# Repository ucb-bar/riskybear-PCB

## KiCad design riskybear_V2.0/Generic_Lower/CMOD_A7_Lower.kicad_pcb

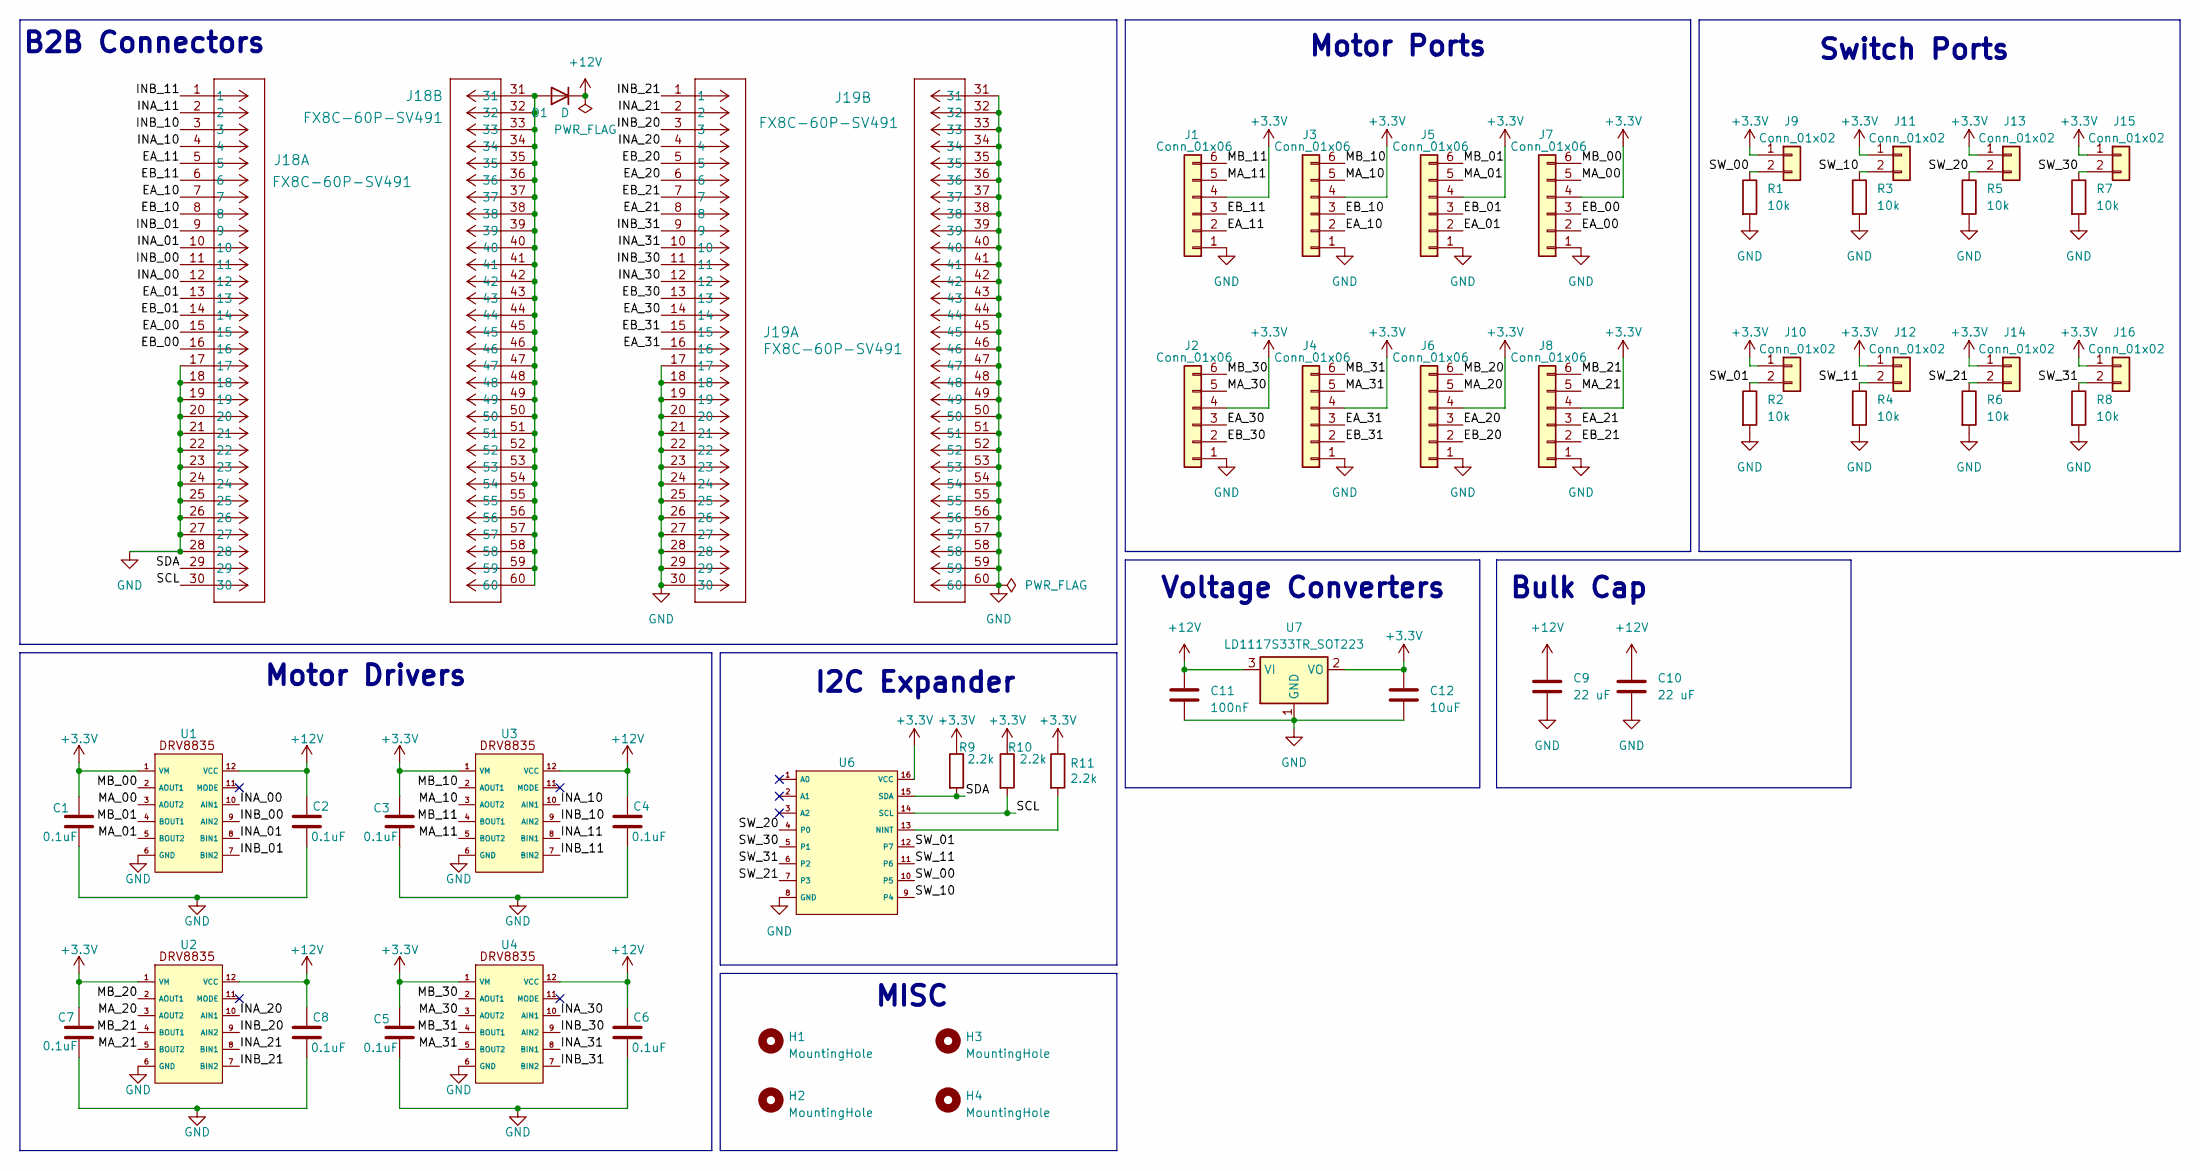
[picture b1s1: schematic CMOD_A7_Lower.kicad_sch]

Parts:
C1, C2, C3, C4, C5, C6, C7, C8: 0.1uF; C_0805_2012Metric
C9, C10: 22 uF; CP_Radial_D5.0mm_P2.00mm
C11: 100nF; C_0805_2012Metric
C12: 10uF; C_0805_2012Metric
D1: D; D_SOD-128
H1, H2, H3, H4: MountingHole; MountingHole_3.2mm_M3
J1, J2, J3, J4, J5, J6, J7, J8: Conn_01x06; JST_SH_BM06B-SRSS-TB_1x06-1MP_P1.00mm_Vertical
J9, J10, J11, J12, J13, J14, J15, J16: Conn_01x02; JST_GH_SM02B-GHS-TB_1x02-1MP_P1.25mm_Horizontal
J18, J19: FX8C-60P-SV491; CONN_P-SV491
R1, R2, R3, R4, R5, R6, R7, R8: 10k; R_0603_1608Metric_Pad0.98x0.95mm_HandSolder
R9, R10, R11: 2.2k; R_0603_1608Metric_Pad0.98x0.95mm_HandSolder
U1, U2, U3, U4: TDFN-12_2x3mm_P0.5mm
U6: TSSOP-16-1EP_4.4x5mm_P0.65mm
U7: LD1117S33TR_SOT223; SOT-223-3_TabPin2

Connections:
+3.3V: C1.1, C3.1, C5.1, C7.1, C12.1, J1.4, J2.4, J3.4, J4.4, J5.4, J6.4, J7.4, J8.4, J9.1, J10.1, J11.1, J12.1, J13.1, J14.1, J15.1, J16.1, R9.1, R10.1, R11.1, U1.1 (VM), U2.1 (VM), U3.1 (VM), U4.1 (VM), U6.16 (VCC), U7.2 (VO)
+12V: C2.1, C4.1, C6.1, C8.1, C9.1, C10.1, C11.1, D1.1 (K), U1.12 (VCC), U2.12 (VCC), U3.12 (VCC), U4.12 (VCC), U7.3 (VI)
/EA_00: J7.2, J18.15
/EA_01: J5.2, J18.13
/EA_10: J3.2, J18.7
/EA_11: J1.2, J18.5
/EA_20: J6.3, J19.6
/EA_21: J8.3, J19.8
/EA_30: J2.3, J19.14
/EA_31: J4.3, J19.16
/EB_00: J7.3, J18.16
/EB_01: J5.3, J18.14
/EB_10: J3.3, J18.8
/EB_11: J1.3, J18.6
/EB_20: J6.2, J19.5
/EB_21: J8.2, J19.7
/EB_30: J2.2, J19.13
/EB_31: J4.2, J19.15
/INA_00: J18.12, U1.10 (AIN1)
/INA_01: J18.10, U1.8 (BIN1)
/INA_10: J18.4, U3.10 (AIN1)
/INA_11: J18.2, U3.8 (BIN1)
/INA_20: J19.4, U2.10 (AIN1)
/INA_21: J19.2, U2.8 (BIN1)
/INA_30: J19.12, U4.10 (AIN1)
/INA_31: J19.10, U4.8 (BIN1)
/INB_00: J18.11, U1.9 (AIN2)
/INB_01: J18.9, U1.7 (BIN2)
/INB_10: J18.3, U3.9 (AIN2)
/INB_11: J18.1, U3.7 (BIN2)
/INB_20: J19.3, U2.9 (AIN2)
/INB_21: J19.1, U2.7 (BIN2)
/INB_30: J19.11, U4.9 (AIN2)
/INB_31: J19.9, U4.7 (BIN2)
/MA_00: J7.5, U1.3 (AOUT2)
/MA_01: J5.5, U1.5 (BOUT2)
/MA_10: J3.5, U3.3 (AOUT2)
/MA_11: J1.5, U3.5 (BOUT2)
/MA_20: J6.5, U2.3 (AOUT2)
/MA_21: J8.5, U2.5 (BOUT2)
/MA_30: J2.5, U4.3 (AOUT2)
/MA_31: J4.5, U4.5 (BOUT2)
/MB_00: J7.6, U1.2 (AOUT1)
/MB_01: J5.6, U1.4 (BOUT1)
/MB_10: J3.6, U3.2 (AOUT1)
/MB_11: J1.6, U3.4 (BOUT1)
/MB_20: J6.6, U2.2 (AOUT1)
/MB_21: J8.6, U2.4 (BOUT1)
/MB_30: J2.6, U4.2 (AOUT1)
/MB_31: J4.6, U4.4 (BOUT1)
/SCL: J18.30, R10.2, U6.14 (SCL)
/SDA: J18.29, R9.2, U6.15 (SDA)
/SW_00: J9.2, R1.1, U6.10 (P5)
/SW_01: J10.2, R2.1, U6.12 (P7)
/SW_10: J11.2, R3.1, U6.9 (P4)
/SW_11: J12.2, R4.1, U6.11 (P6)
/SW_20: J13.2, R5.1, U6.4 (P0)
/SW_21: J14.2, R6.1, U6.7 (P3)
/SW_30: J15.2, R7.1, U6.5 (P1)
/SW_31: J16.2, R8.1, U6.6 (P2)
GND: C1.2, C2.2, C3.2, C4.2, C5.2, C6.2, C7.2, C8.2, C9.2, C10.2, C11.2, C12.2, J1.1, J2.1, J3.1, J4.1, J5.1, J6.1, J7.1, J8.1, J18.17, J18.18, J18.19, J18.20, J18.21, J18.22, J18.23, J18.24, J18.25, J18.26, J18.27, J18.28, J19.17, J19.18, J19.19, J19.20, J19.21, J19.22, J19.23, J19.24, J19.25, J19.26, J19.27, J19.28, J19.29, J19.30, J19.31, J19.32, J19.33, J19.34, J19.35, J19.36, J19.37, J19.38, J19.39, J19.40, J19.41, J19.42, J19.43, J19.44, J19.45, J19.46, J19.47, J19.48, J19.49, J19.50, J19.51, J19.52, J19.53, J19.54, J19.55, J19.56, J19.57, J19.58, J19.59, J19.60, R1.2, R2.2, R3.2, R4.2, R5.2, R6.2, R7.2, R8.2, U1.6 (GND), U2.6 (GND), U3.6 (GND), U4.6 (GND), U6.8 (GND), U7.1 (GND)
unnamed: D1.2 (A), J18.31, J18.32, J18.33, J18.34, J18.35, J18.36, J18.37, J18.38, J18.39, J18.40, J18.41, J18.42, J18.43, J18.44, J18.45, J18.46, J18.47, J18.48, J18.49, J18.50, J18.51, J18.52, J18.53, J18.54, J18.55, J18.56, J18.57, J18.58, J18.59, J18.60
unnamed: R11.2, U6.13 (NINT)

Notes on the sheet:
B2B Connectors
Bulk Cap
Voltage Converters
I2C Expander
Motor Ports
Switch Ports
MISC
Motor Drivers

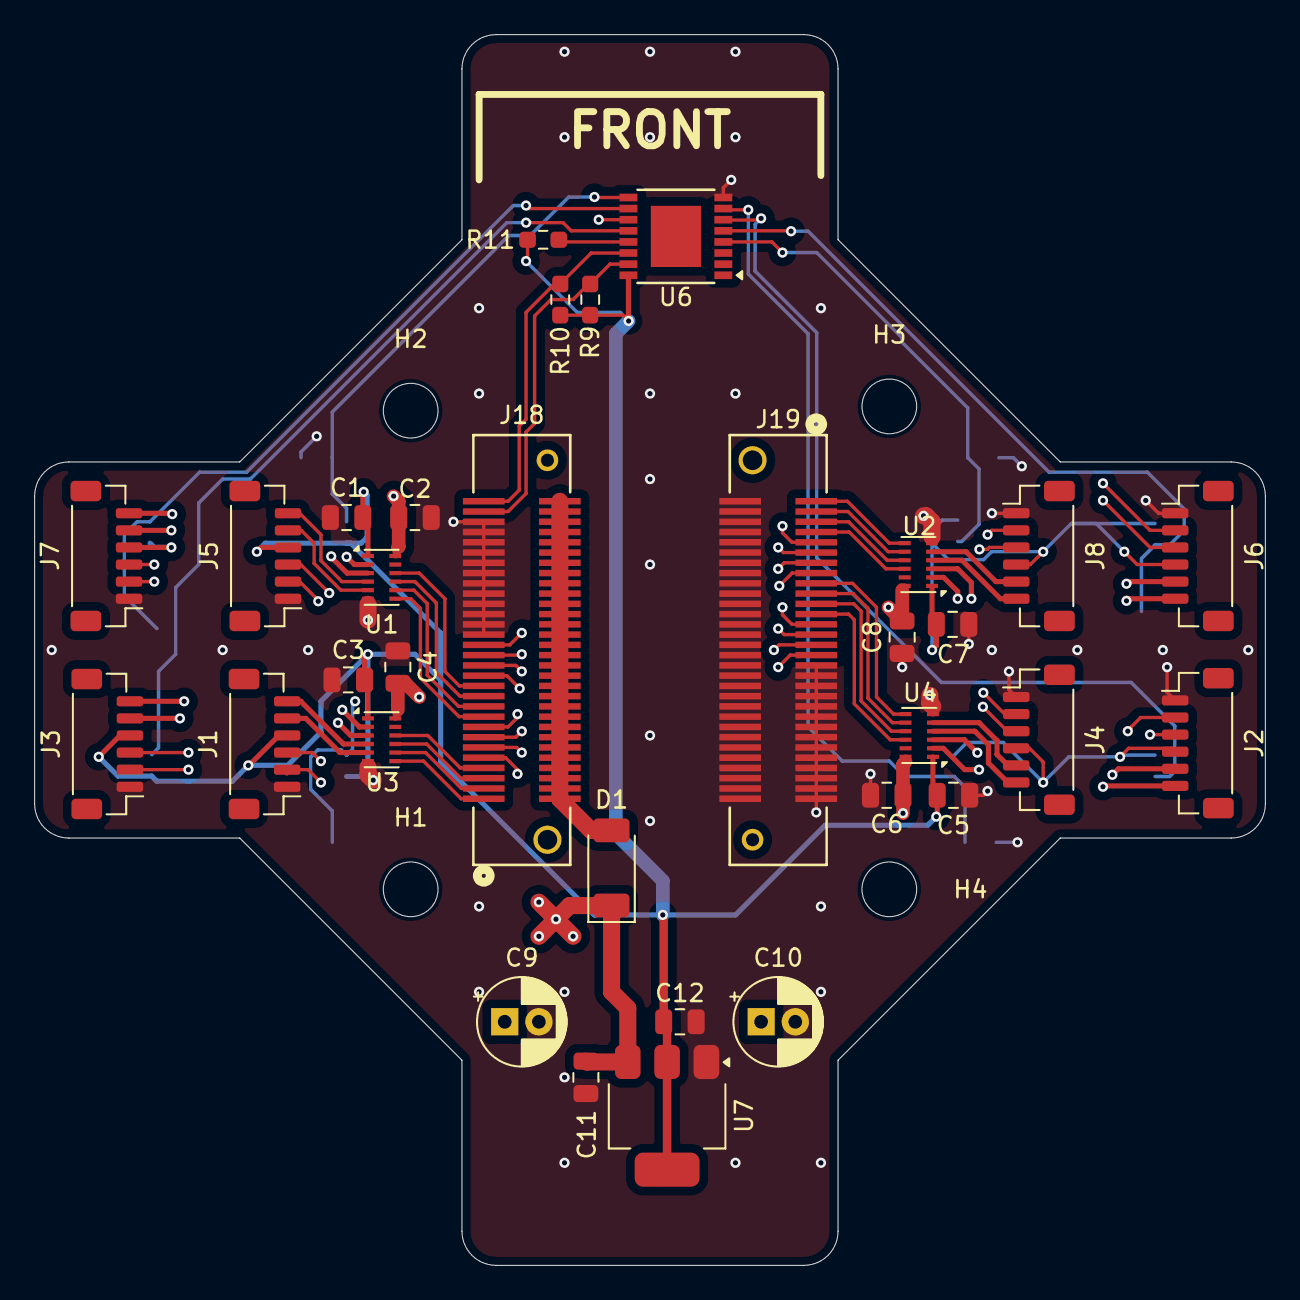
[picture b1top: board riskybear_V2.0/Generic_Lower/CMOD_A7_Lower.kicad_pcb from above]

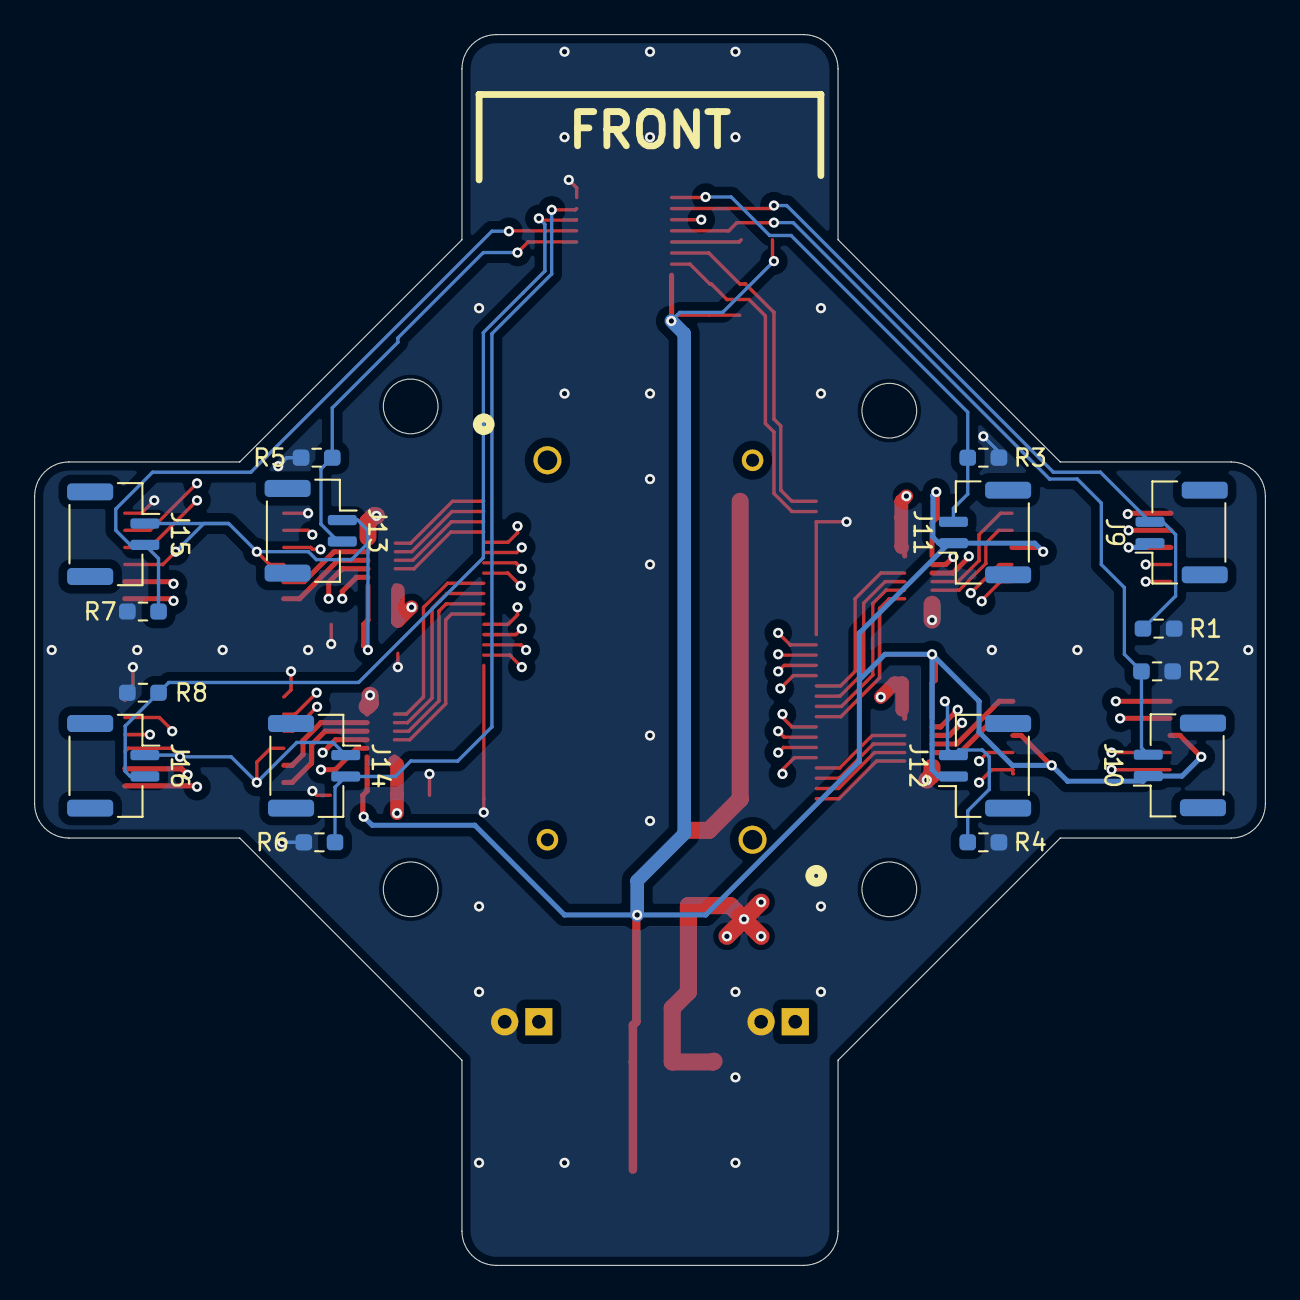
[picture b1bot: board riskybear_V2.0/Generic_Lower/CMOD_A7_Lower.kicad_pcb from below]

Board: 4 copper layers, 72.0 x 72.0 mm, 52 parts (16 on the bottom side), 63 nets.

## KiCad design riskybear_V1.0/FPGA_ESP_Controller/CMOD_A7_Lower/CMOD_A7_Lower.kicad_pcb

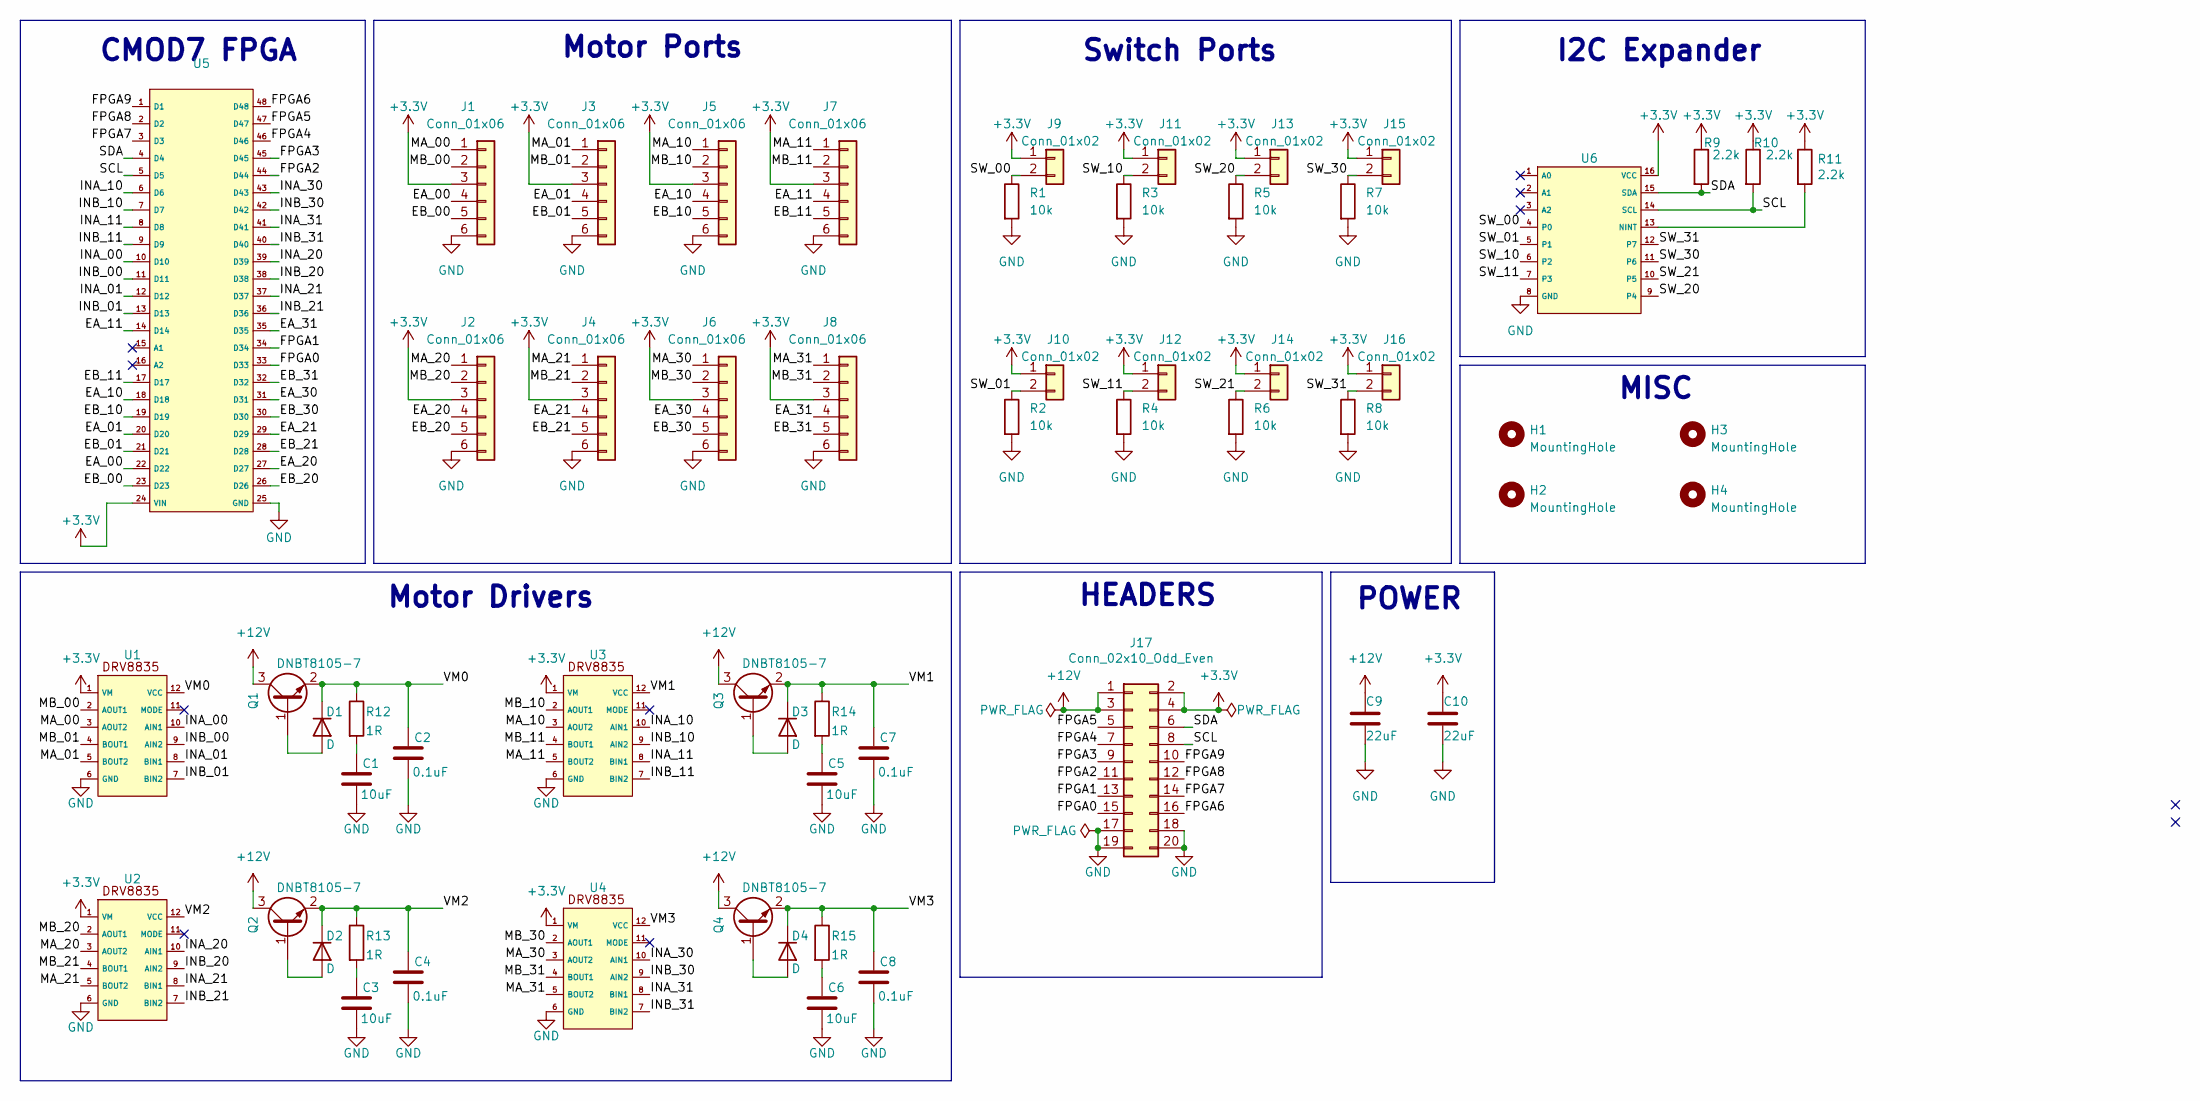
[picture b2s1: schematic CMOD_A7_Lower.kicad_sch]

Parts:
C1, C3, C5, C6: 10uF; C_0805_2012Metric
C2, C4, C7, C8: 0.1uF; C_0805_2012Metric
C9, C10: 22uF; CP_Radial_D5.0mm_P2.00mm
D1, D2, D3, D4: D; D_SMA
H1, H2, H3, H4: MountingHole; MountingHole_3.2mm_M3
J1, J2, J3, J4, J5, J6, J7, J8: Conn_01x06; JST_SH_BM06B-SRSS-TB_1x06-1MP_P1.00mm_Vertical
J9, J10, J11, J12, J13, J14, J15, J16: Conn_01x02; PinHeader_1x02_P2.54mm_Vertical_SMD_Pin1Left
J17: Conn_02x10_Odd_Even; PinHeader_2x10_P2.54mm_Vertical
Q1, Q2, Q3, Q4: DNBT8105-7; SOT-23
R1, R2, R3, R4, R5, R6, R7, R8: 10k; R_0603_1608Metric_Pad0.98x0.95mm_HandSolder
R9, R10, R11: 2.2k; R_0603_1608Metric_Pad0.98x0.95mm_HandSolder
R12, R13, R14, R15: 1R; C_0603_1608Metric
U1, U2, U3, U4: TDFN-12_2x3mm_P0.5mm
U5: CMODA7
U6: TSSOP-16-1EP_4.4x5mm_P0.65mm

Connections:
+3.3V: C10.1, J1.3, J2.3, J3.3, J4.3, J5.3, J6.3, J7.3, J8.3, J9.1, J10.1, J11.1, J12.1, J13.1, J14.1, J15.1, J16.1, J17.2, J17.4, R9.1, R10.1, R11.1, U1.1 (VM), U2.1 (VM), U3.1 (VM), U4.1 (VM), U5.24 (VIN), U6.16 (VCC)
+12V: C9.1, J17.1, J17.3, Q1.3 (C), Q2.3 (C), Q3.3 (C), Q4.3 (C)
/EA_00: J1.4, U5.22 (D22)
/EA_01: J3.4, U5.20 (D20)
/EA_10: J5.4, U5.18 (D18)
/EA_11: J7.4, U5.14 (D14)
/EA_20: J2.4, U5.27 (D27)
/EA_21: J4.4, U5.29 (D29)
/EA_30: J6.4, U5.31 (D31)
/EA_31: J8.4, U5.35 (D35)
/EB_00: J1.5, U5.23 (D23)
/EB_01: J3.5, U5.21 (D21)
/EB_10: J5.5, U5.19 (D19)
/EB_11: J7.5, U5.17 (D17)
/EB_20: J2.5, U5.26 (D26)
/EB_21: J4.5, U5.28 (D28)
/EB_30: J6.5, U5.30 (D30)
/EB_31: J8.5, U5.32 (D32)
/FPGA0: J17.15, U5.33 (D33)
/FPGA1: J17.13, U5.34 (D34)
/FPGA2: J17.11, U5.44 (D44)
/FPGA3: J17.9, U5.45 (D45)
/FPGA4: J17.7, U5.46 (D46)
/FPGA5: J17.5, U5.47 (D47)
/FPGA6: J17.16, U5.48 (D48)
/FPGA7: J17.14, U5.3 (D3)
/FPGA8: J17.12, U5.2 (D2)
/FPGA9: J17.10, U5.1 (D1)
/INA_00: U1.10 (AIN1), U5.10 (D10)
/INA_01: U1.8 (BIN1), U5.12 (D12)
/INA_10: U3.10 (AIN1), U5.6 (D6)
/INA_11: U3.8 (BIN1), U5.8 (D8)
/INA_20: U2.10 (AIN1), U5.39 (D39)
/INA_21: U2.8 (BIN1), U5.37 (D37)
/INA_30: U4.10 (AIN1), U5.43 (D43)
/INA_31: U4.8 (BIN1), U5.41 (D41)
/INB_00: U1.9 (AIN2), U5.11 (D11)
/INB_01: U1.7 (BIN2), U5.13 (D13)
/INB_10: U3.9 (AIN2), U5.7 (D7)
/INB_11: U3.7 (BIN2), U5.9 (D9)
/INB_20: U2.9 (AIN2), U5.38 (D38)
/INB_21: U2.7 (BIN2), U5.36 (D36)
/INB_30: U4.9 (AIN2), U5.42 (D42)
/INB_31: U4.7 (BIN2), U5.40 (D40)
/MA_00: J1.1, U1.3 (AOUT2)
/MA_01: J3.1, U1.5 (BOUT2)
/MA_10: J5.1, U3.3 (AOUT2)
/MA_11: J7.1, U3.5 (BOUT2)
/MA_20: J2.1, U2.3 (AOUT2)
/MA_21: J4.1, U2.5 (BOUT2)
/MA_30: J6.1, U4.3 (AOUT2)
/MA_31: J8.1, U4.5 (BOUT2)
/MB_00: J1.2, U1.2 (AOUT1)
/MB_01: J3.2, U1.4 (BOUT1)
/MB_10: J5.2, U3.2 (AOUT1)
/MB_11: J7.2, U3.4 (BOUT1)
/MB_20: J2.2, U2.2 (AOUT1)
/MB_21: J4.2, U2.4 (BOUT1)
/MB_30: J6.2, U4.2 (AOUT1)
/MB_31: J8.2, U4.4 (BOUT1)
/SCL: J17.8, R10.2, U5.5 (D5), U6.14 (SCL)
/SDA: J17.6, R9.2, U5.4 (D4), U6.15 (SDA)
/SW_00: J9.2, R1.1, U6.4 (P0)
/SW_01: J10.2, R2.1, U6.5 (P1)
/SW_10: J11.2, R3.1, U6.6 (P2)
/SW_11: J12.2, R4.1, U6.7 (P3)
/SW_20: J13.2, R5.1, U6.9 (P4)
/SW_21: J14.2, R6.1, U6.10 (P5)
/SW_30: J15.2, R7.1, U6.11 (P6)
/SW_31: J16.2, R8.1, U6.12 (P7)
/VM0: C2.1, D1.1 (K), Q1.2 (E), R12.1, U1.12 (VCC)
/VM1: C7.1, D3.1 (K), Q3.2 (E), R14.1, U3.12 (VCC)
/VM2: C4.1, D2.1 (K), Q2.2 (E), R13.1, U2.12 (VCC)
/VM3: C8.1, D4.1 (K), Q4.2 (E), R15.1, U4.12 (VCC)
GND: C1.2, C2.2, C3.2, C4.2, C5.2, C6.2, C7.2, C8.2, C9.2, C10.2, J1.6, J2.6, J3.6, J4.6, J5.6, J6.6, J7.6, J8.6, J17.17, J17.18, J17.19, J17.20, R1.2, R2.2, R3.2, R4.2, R5.2, R6.2, R7.2, R8.2, U1.6 (GND), U2.6 (GND), U3.6 (GND), U4.6 (GND), U5.25 (GND), U6.8 (GND)
unnamed: C1.1, R12.2
unnamed: C3.1, R13.2
unnamed: C5.1, R14.2
unnamed: C6.1, R15.2
unnamed: D1.2 (A), Q1.1 (B)
unnamed: D2.2 (A), Q2.1 (B)
unnamed: D3.2 (A), Q3.1 (B)
unnamed: D4.2 (A), Q4.1 (B)
unnamed: R11.2, U6.13 (NINT)

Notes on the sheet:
CMOD7 FPGA
I2C Expander
Motor Ports
Switch Ports
POWER
MISC
Motor Drivers
HEADERS

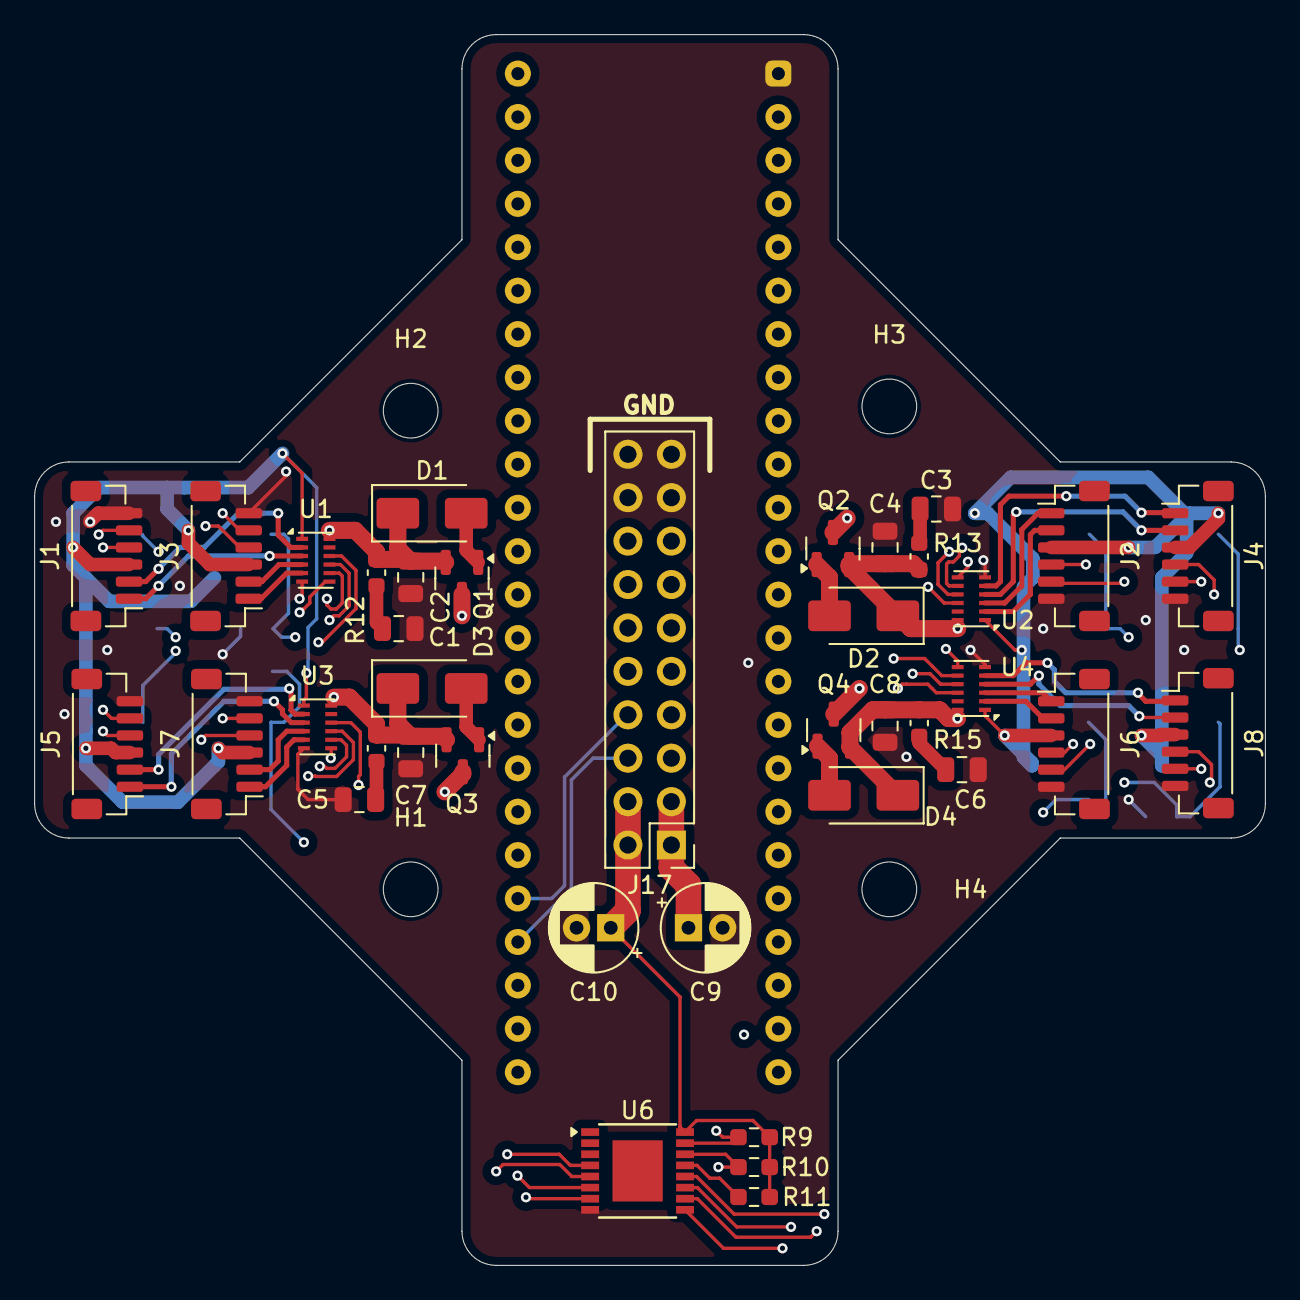
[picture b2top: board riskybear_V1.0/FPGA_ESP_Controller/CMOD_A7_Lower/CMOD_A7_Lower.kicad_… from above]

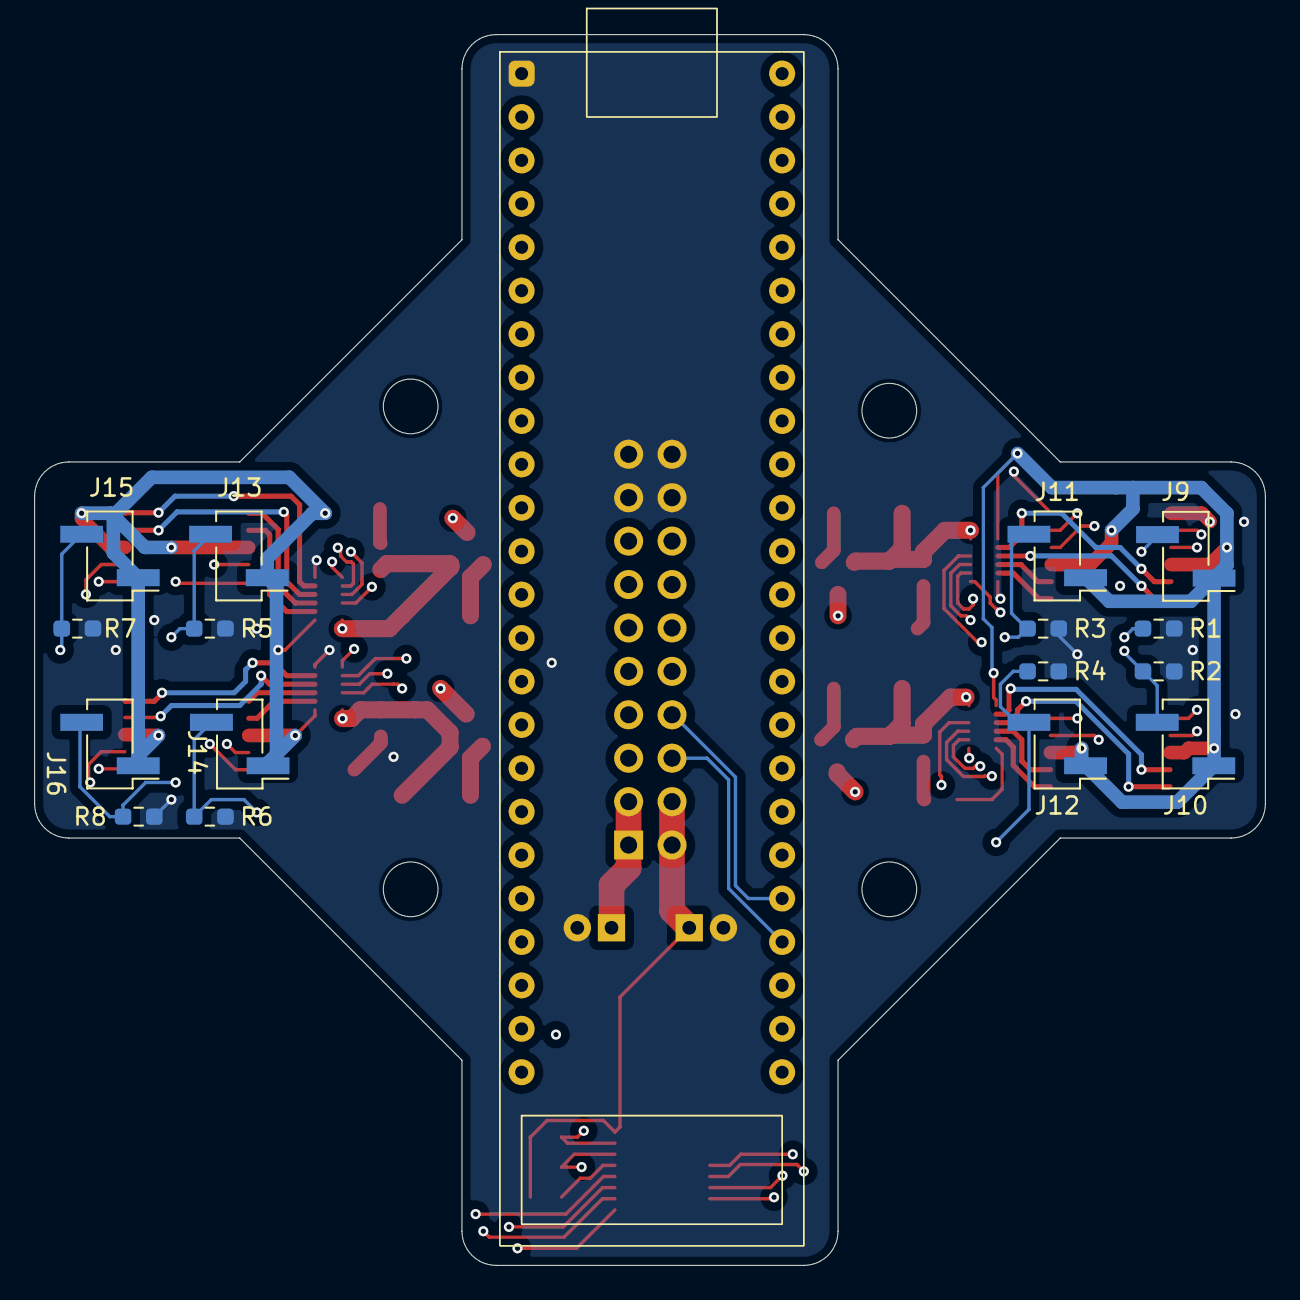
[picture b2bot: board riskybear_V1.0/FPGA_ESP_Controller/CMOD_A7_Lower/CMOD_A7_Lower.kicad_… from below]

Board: 4 copper layers, 72.0 x 72.0 mm, 60 parts (17 on the bottom side), 84 nets.

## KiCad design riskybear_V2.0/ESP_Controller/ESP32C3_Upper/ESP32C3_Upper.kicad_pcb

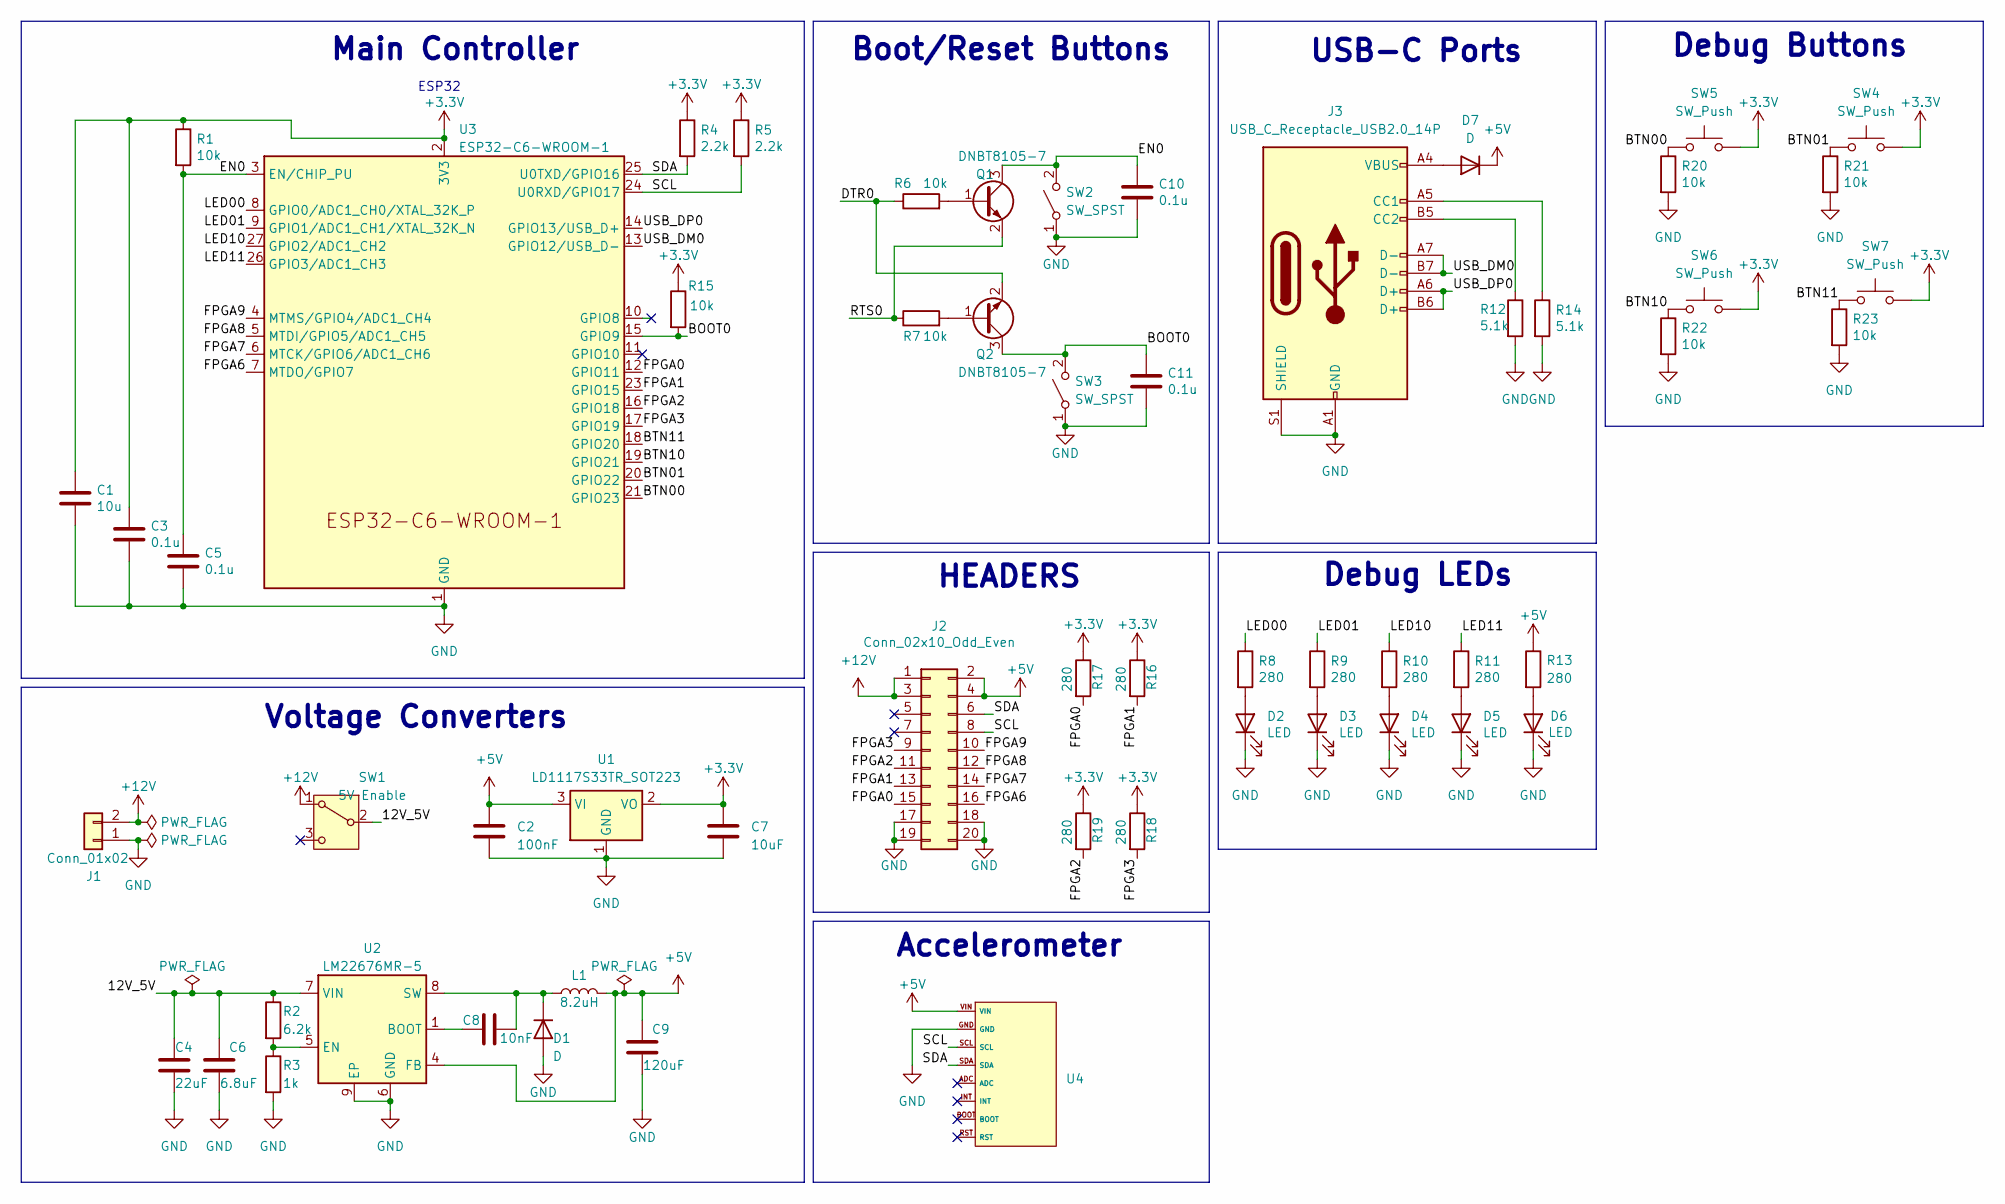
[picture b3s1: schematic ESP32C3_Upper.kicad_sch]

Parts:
C1: 10u; C_0603_1608Metric_Pad1.08x0.95mm_HandSolder
C2: 100nF; C_0805_2012Metric
C3, C5, C10, C11: 0.1u; C_0603_1608Metric_Pad1.08x0.95mm_HandSolder
C4: 22uF; CP_Radial_D5.0mm_P2.00mm
C6: 6.8uF; C_0805_2012Metric
C7: 10uF; C_0805_2012Metric
C8: 10nF; C_0805_2012Metric
C9: 120uF; CP_Radial_D6.3mm_P2.50mm
D1, D7: D; D_SMA_Handsoldering
D2, D3, D4, D5, D6: LED; LED_0805_2012Metric_Pad1.15x1.40mm_HandSolder
J1: Conn_01x02; JST_XA_B02B-XASK-1_1x02_P2.50mm_Vertical
J2: Conn_02x10_Odd_Even; PinHeader_2x10_P2.54mm_Vertical
J3: USB_C_Receptacle_USB2.0_14P; USB_C_Receptacle_JAE_DX07S016JA1R1500
L1: 8.2uH; L_7.3x7.3_H3.5
Q1, Q2: DNBT8105-7; SOT-23
R1, R6, R7, R15, R20, R21, R22, R23: 10k; R_0603_1608Metric_Pad0.98x0.95mm_HandSolder
R2: 6.2k; R_0805_2012Metric
R3: 1k; R_0805_2012Metric
R4, R5: 2.2k; R_0603_1608Metric_Pad0.98x0.95mm_HandSolder
R8, R9, R10, R11, R13, R16, R17, R18, R19: 280; R_0603_1608Metric_Pad0.98x0.95mm_HandSolder
R12, R14: 5.1k; R_0603_1608Metric_Pad0.98x0.95mm_HandSolder
SW1: 5V Enable; SW_Slide-03_Wuerth-WS-SLTV_10x2.5x6.4_P2.54mm
SW2, SW3: SW_SPST; SW_SPST_B3U-1000P
SW4, SW5, SW6, SW7: SW_Push; SW_SPST_B3U-1000P
U1: LD1117S33TR_SOT223; SOT-223-3_TabPin2
U2: LM22676MR-5; TI_SO-PowerPAD-8
U3: ESP32-C6-WROOM-1
U4: BNO055

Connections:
+3.3V: C1.1, C3.1, C7.1, R1.1, R4.1, R5.1, R15.1, R16.1, R17.1, R18.1, R19.1, SW4.2, SW5.2, SW6.2, SW7.2, U1.2 (VO), U3.2 (3V3)
+5V: C2.1, C9.1, D7.1 (K), J2.2, J2.4, L1.2, R13.1, U1.3 (VI), U2.4 (FB), U4.VIN
+12V: J1.2, J2.1, J2.3, SW1.1 (A)
/12V_5V: C4.1, C6.1, R2.1, SW1.2 (B), U2.7 (VIN)
/BOOT0: C11.1, Q2.3 (C), R15.2, SW3.2 (B), U3.15 (GPIO9)
/BTN00: R20.1, SW5.1, U3.21 (GPIO23)
/BTN01: R21.1, SW4.1, U3.20 (GPIO22)
/BTN10: R22.1, SW6.1, U3.19 (GPIO21)
/BTN11: R23.1, SW7.1, U3.18 (GPIO20)
/DTR0: Q2.2 (E), R6.1
/EN0: C5.1, C10.1, Q1.3 (C), R1.2, SW2.2 (B), U3.3 (EN/CHIP_PU)
/FPGA0: J2.15, R17.2, U3.12 (GPIO11)
/FPGA1: J2.13, R16.2, U3.23 (GPIO15)
/FPGA2: J2.11, R19.2, U3.16 (GPIO18)
/FPGA3: J2.9, R18.2, U3.17 (GPIO19)
/FPGA6: J2.16, U3.7 (MTDO/GPIO7)
/FPGA7: J2.14, U3.6 (MTCK/GPIO6/ADC1_CH6)
/FPGA8: J2.12, U3.5 (MTDI/GPIO5/ADC1_CH5)
/FPGA9: J2.10, U3.4 (MTMS/GPIO4/ADC1_CH4)
/LED00: R8.1, U3.8 (GPIO0/ADC1_CH0/XTAL_32K_P)
/LED01: R9.1, U3.9 (GPIO1/ADC1_CH1/XTAL_32K_N)
/LED10: R10.1, U3.27 (GPIO2/ADC1_CH2)
/LED11: R11.1, U3.26 (GPIO3/ADC1_CH3)
/RTS0: Q1.2 (E), R7.1
/SCL: J2.8, R5.2, U3.24 (U0RXD/GPIO17), U4.SCL
/SDA: J2.6, R4.2, U3.25 (U0TXD/GPIO16), U4.SDA
/USB_DM0: J3.A7 (D-), J3.B7 (D-), U3.13 (GPIO12/USB_D-)
/USB_DP0: J3.A6 (D+), J3.B6 (D+), U3.14 (GPIO13/USB_D+)
GND: C1.2, C2.2, C3.2, C4.2, C5.2, C6.2, C7.2, C9.2, C10.2, C11.2, D1.2 (A), D2.1 (K), D3.1 (K), D4.1 (K), D5.1 (K), D6.1 (K), J1.1, J2.17, J2.18, J2.19, J2.20, J3.A1 (GND), J3.A12 (GND), J3.B1 (GND), J3.B12 (GND), J3.S1 (SHIELD), R3.2, R12.2, R14.2, R20.2, R21.2, R22.2, R23.2, SW2.1 (A), SW3.1 (A), U1.1 (GND), U2.6 (GND), U2.9 (EP), U3.1 (GND), U3.28 (GND), U3.29 (GND), U4.GND
unnamed: C8.2, D1.1 (K), L1.1, U2.8 (SW)
unnamed: D2.2 (A), R8.2
unnamed: D3.2 (A), R9.2
unnamed: D4.2 (A), R10.2
unnamed: D5.2 (A), R11.2
unnamed: D6.2 (A), R13.2
unnamed: D7.2 (A), J3.A4 (VBUS), J3.A9 (VBUS), J3.B4 (VBUS), J3.B9 (VBUS)
unnamed: J3.A5 (CC1), R14.1
unnamed: J3.B5 (CC2), R12.1
unnamed: Q1.1 (B), R6.2
unnamed: Q2.1 (B), R7.2
unnamed: C8.1, U2.1 (BOOT)
unnamed: R2.2, R3.1, U2.5 (EN)

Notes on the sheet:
Debug Buttons
Accelerometer
USB-C Ports
Voltage Converters
ESP32
Main Controller
Boot/Reset Buttons
HEADERS
Debug LEDs
